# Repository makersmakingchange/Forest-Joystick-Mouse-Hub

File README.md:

# Forest Joystick Mouse Hub

## Overview
The Forest Hub enables a user to connect an analog joystick and up to four assistive switches to emulate a USB Mouse or USB Gamepad. As a USB Mouse, the joystick controls cursor movement and the assistive switches activate the left mouse button, right mouse button, middle mouse button, and scroll. As a USB Mouse, the joystick maps to the joystick/thumbstick and the assistive switches map to the joystick buttons. An additional assistive switch can be attached to the Hub to cycle between three setting slots and change the output mode between USB Mouse mode and USB Gamepad mode.

The device is comprised of a custom printed circuit board, off-the-shelf electronics, and 3D printed parts. The overall cost of materials for a single build is about $100. The individual unit cost cost is closer to $55. 

The Forest Hub is open assistive technology (OpenAT). Under the terms of the open source licenses, the device may be built, used, and improved upon by anyone.

Last updated: 2024-Apr-17
The latest version (V2.1) includes a new easier to use LED jig, updated firmware with center calibration, and updated documentation.
An updated version of the PCB and enclosure has been released (V2.0.1, 2024-Feb-20). The last version of the Forest Hub (v2.0.1) has been built and tested.

MMC Assistive Device Library Listing: https://makersmakingchange.com/s/product/forest-joystick-mouse-hub/01tJR000000E4bdYAC

## OpenAT Joysticks
This design is part of the [OpenAT Joystick Project](https://github.com/makersmakingchange/OpenAT-Joysticks), a collection of open source designs for digital access and adapted gaming.  

## How to Obtain the Device
### 1. Do-it-Yourself (DIY) or Do-it-Together (DIT)

This is an open-source assistive technology, so anyone is free to build it. All of the files and instructions required to build the device are contained within this repository. Refer to the Maker Guide below.

### 2. Request a build of this device

If you would like to obtain a Forest Hub, you may submit a build request through the [MMC Assistive Device Library Listing](https://makersmakingchange.com/s/product/forest-joystick-mouse-hub/01tJR000000E4bdYAC) to have a volunteer maker build the device. As the requestor, you are responsible for reimbursing the maker for the cost of materials and any shipping.

### 3. Build this device for someone else

If you have the skills and equipment to build this device, and would like to donate your time to create the switch for someone who needs it, visit the [MMC Maker Wanted](https://makersmakingchange.com/maker-wanted/) section.

## Build Instructions

### 1. Read through the Maker Guide

The [Maker Guide](/Documentation/Forest_Hub_Maker_Guide.pdf) contains all the necessary information to build the device.

### 2. Use the Maker Checklist
Use the Maker Checklist in the [Maker Guide](/Documentation/Forest_Hub_Maker_Guide.pdf) to confirm details and customization options with the user.

### 3. Order the Custom Printed Circuit Board (PCB)
The manufacturing files for the PCB are located in the [PCB_Build_Files](/Build_Files/PCB_Build_Files/) folder.

### 4. Order the Off-The-Shelf Components

The [Bill of Materials](/Documentation/Forest_Hub_BOM.xlsx) lists all of the parts and 3D printed components required to build the device. 

### 5. Print the 3D Printable components

The print files can be found in the [/Build_Files/3D_Printing_Files](/Build_Files/3D_Printing/) folder.

### 6.  Assemble the Device

Reference the Assembly Guide section in the [Maker Guide](/Documentation/Forest_Hub_Maker_Guide.pdf) for the tools and steps required to build the device.

## Files
### Documentation
| Document             | Version | Link |
|----------------------|---------|------|
| Design Rationale     | 2.1     | [Forest_Hub_Design_Rationale](/Documentation/Forest_Hub_Design_Rationale.pdf)     |
| Maker Guide          | 2.1     | [Forest_Hub_Maker_Guide](/Documentation/Forest_Hub_Maker_Guide.pdf)     |
| Bill of Materials    | 2.1     | [Forest_Hub_Bill_of_Materials](/Documentation/Forest_Hub_BOM.csv)     |
| User Guide           | 2.1     | [Forest_Hub_User_Guide](/Documentation/Forest_Hub_User_Guide.pdf)    |
| Changelog            | 2.1     | [Changes](Changes.txt)     |

### Design Files
 - [CAD design Files](/Design_Files/CAD_Design_Files)
 - [PCB Design Files](/Design_Files/PCB_Design_Files)

### Build Files
 - [3D Printing Files](/Build_Files/3D_Printing_Files)
 - [PCB Build Files](/Build_Files/PCB_Build_Files/)
 - [Firmware Files](/Build_Files/Firmware_Files)

## License
Copyright (c) 2023 Neil Squire Society.

This repository describes Open Hardware:
 - Everything needed or used to design, make, test, or prepare the Forest Hub is licensed under the [CERN 2.0 Weakly Reciprocal license (CERN-OHL-W v2) or later](https://cern.ch/cern-ohl ) .
 - All software is under the [GNU General Public License v3.0 (GPL-3.0)](https://www.gnu.org/licenses/gpl.html).
 - Accompanying material such as instruction manuals, videos, and other copyrightable works that are useful but not necessary to design, make, test, or prepare the Forest Hub are published under a [Creative Commons Attribution-ShareAlike 4.0 license (CC BY-SA 4.0)](https://creativecommons.org/licenses/by-sa/4.0/) .

You may redistribute and modify this documentation and make products using it under the terms of the [CERN-OHL-W v2](https://cern.ch/cern-ohl).
This documentation is distributed WITHOUT ANY EXPRESS OR IMPLIED WARRANTY, INCLUDING OF MERCHANTABILITY, SATISFACTORY QUALITY AND FITNESS FOR A PARTICULAR PURPOSE.
Please see the CERN-OHL-W v2 for applicable conditions.

Source Location: https://github.com/makersmakingchange/Forest-Joystick-Mouse-Hub

## Attribution

The [Adafruit QT Py](http://www.adafruit.com/products/4600) development board was designed by Limor Fried/Ladyada from Adafruit. The PCB design is [available open source](https://github.com/adafruit/Adafruit-QT-Py-PCB) under a CC-BY-SA license.

The concept for the Forest Hub was based on the [Enabled Controller Mini](https://github.com/milador/Enabled-Controller-Mini) by [Milador](https://github.com/milador).

### Contributors
- Jake McIvor, Neil Squire Society. Concept generation, enclosure design, schematic and PCB design, coding, documentation, testing.
- Milad Ha, Neil Squire Society. Schematic and PCB design, coding.
- Josie Versloot, Neil Squire Society. Concept generation, coding, documentation.
- Derrick Andrews, Neil Squire Society. Schematic design.
- Stephen Moyer, Neil Squire Society. Concept generation.
- Tyler Fentie, Neil Squire Society. Concept generation

## Open Source Hardware Certification

The Forest Hub has been certified as open source hardware by the Open Source Hardware Association under the OSHWA UID [CA000033](https://certification.oshwa.org/ca000033.html).

---
<!-- ABOUT MMC START -->
## About Makers Making Change

Makers Making Change is a program of [Neil Squire](https://www.neilsquire.ca/), a Canadian non-profit that uses technology, knowledge, and passion to empower people with disabilities.

Makers Making Change leverages the capacity of community based Makers, Disability Professionals and Volunteers to develop and deliver affordable Open Source Assistive Technologies.

 - Website: [www.MakersMakingChange.com](https://www.makersmakingchange.com/)
 - GitHub: [makersmakingchange](https://github.com/makersmakingchange)
 - Bluesky: [@makersmakingchange.bsky.social](https://bsky.app/profile/makersmakingchange.bsky.social)
 - Instagram: [@makersmakingchange](https://www.instagram.com/makersmakingchange)
 - Facebook: [makersmakechange](https://www.facebook.com/makersmakechange)
 - LinkedIn: [Neil Squire Society](https://www.linkedin.com/company/neil-squire-society/)
 - Thingiverse: [makersmakingchange](https://www.thingiverse.com/makersmakingchange/about)
 - Printables: [MakersMakingChange](https://www.printables.com/@MakersMakingChange)

### Contact Us
For technical questions, to get involved, or to share your experience we encourage you to [visit our website](https://www.makersmakingchange.com/) or [contact us](https://www.makersmakingchange.com/s/contact).
<!-- ABOUT MMC END -->

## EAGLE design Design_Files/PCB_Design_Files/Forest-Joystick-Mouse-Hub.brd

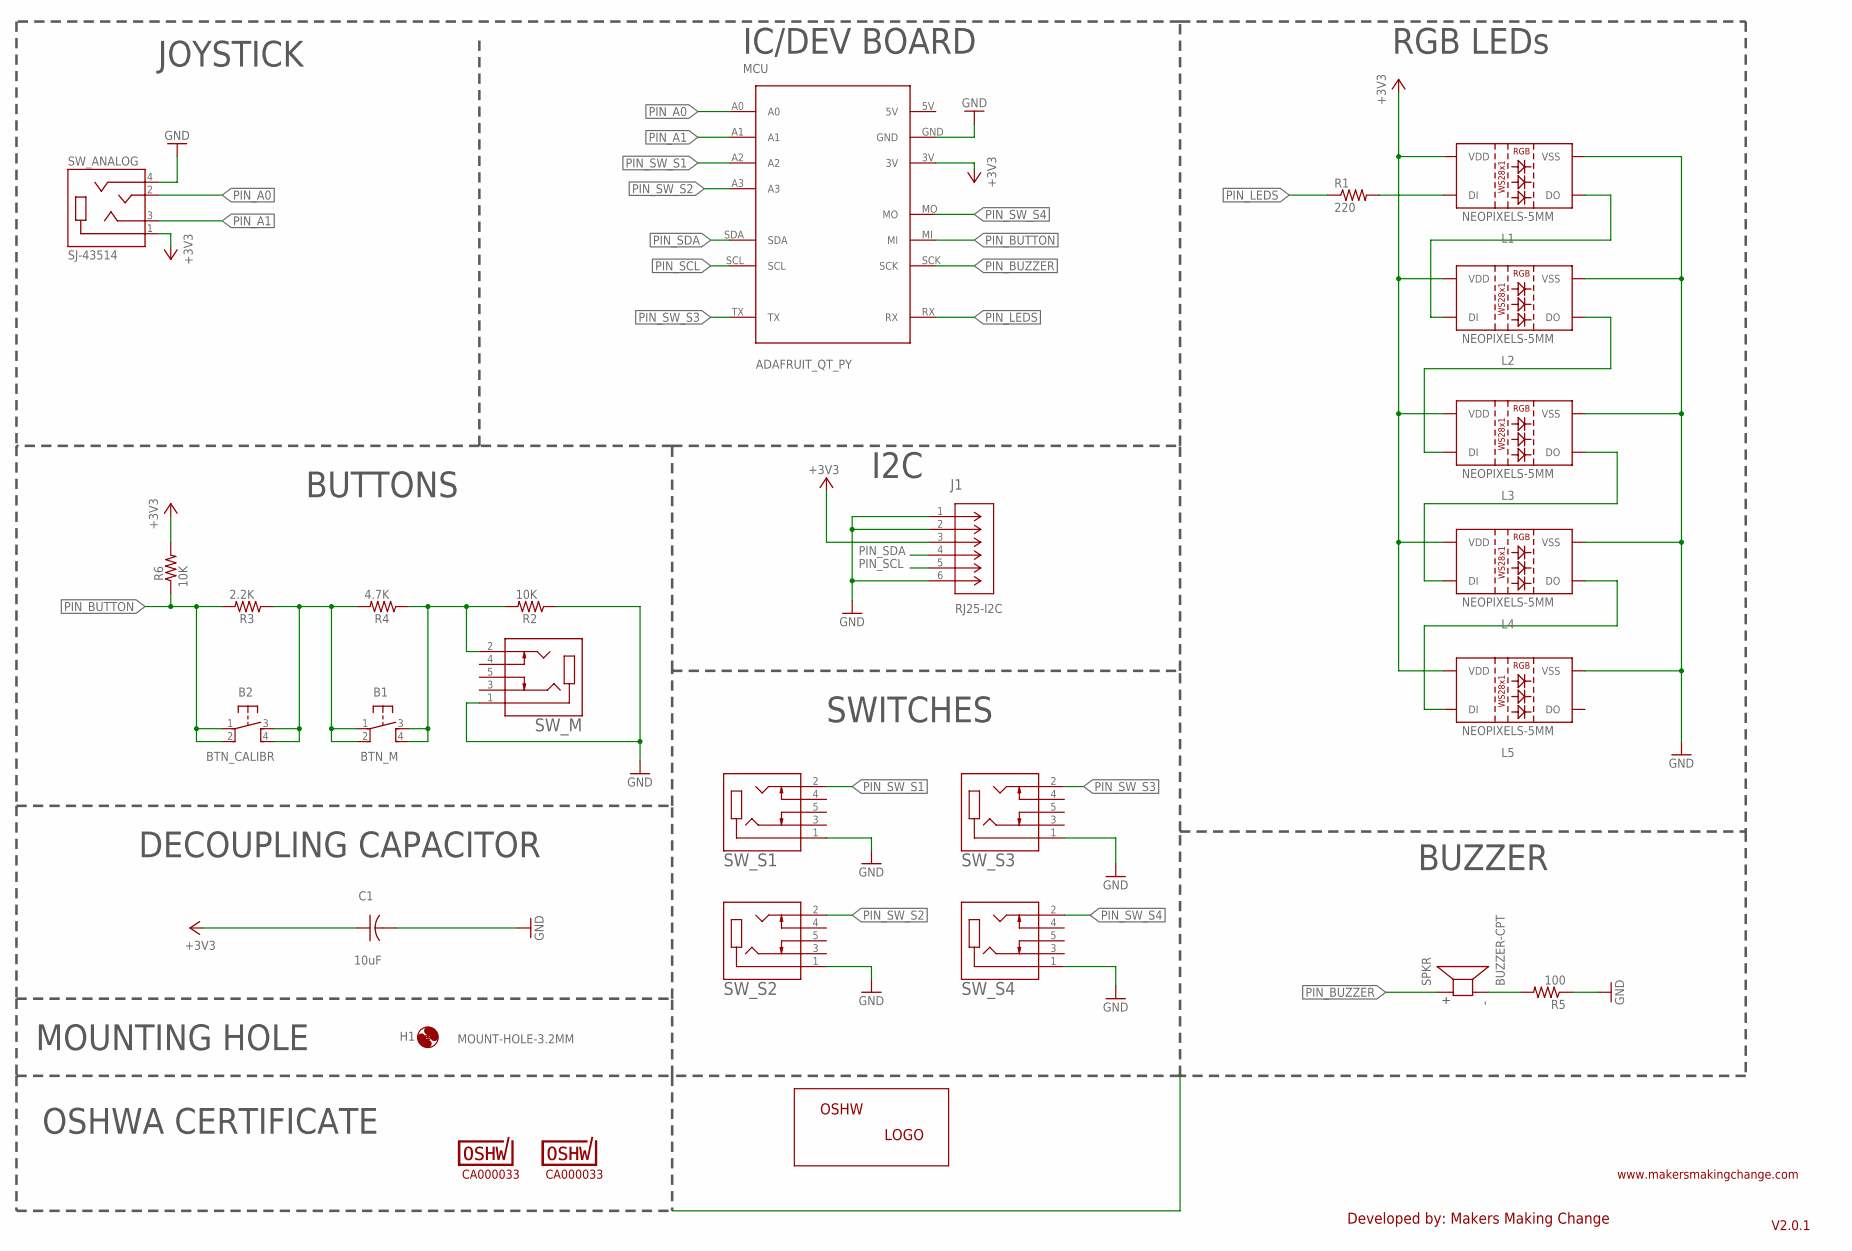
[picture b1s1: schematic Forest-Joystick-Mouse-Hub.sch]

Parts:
B1: BTN_M; B3F-5050
B2: BTN_CALIBR; B3F-5050
C1: 10uF; CAP-050-030X075
H1: MOUNT-HOLE-3.2MM; HOLE-3.2MM
J1: 5555165-1; CONN6_5555165-1
L1, L2, L3, L4, L5: NEOPIXELS-5MM
LOGO-OSHWA: CA000033; OSHWA-CERT-SMALL-SILK
MCU: ADAFRUIT_QT_PY; QT_PY
R1: 220; RESISTOR_0206/8
R2, R6: 10K; RESISTOR_0206/8
R3: 2.2K; RESISTOR_0206/8
R4: 4.7K; RESISTOR_0206/8
R5: 100; RESISTOR_0206/8
SPKR: BUZZER-CPT; CUI_CPT-1255C-090
SW_ANALOG: SJ-43514; CUI_SJ-43514
SW_M: CUI_SJ1-3535NGSJ1-3535NG; CUI_SJ1-3535NG
SW_S1, SW_S2, SW_S3, SW_S4: CUI_SJ1-3535NGSJ1-3535NG; CUI_SJ1-3535NG
U$3: OSHW_LOGO-XSM; OSHW_X-SMALL_LOGO
U$4: CA000033; OSHWA-CERT-SMALL-SILK

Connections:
+3V3: C1.1, J1.3, L1.P2 (VDD), L2.P2 (VDD), L3.P2 (VDD), L4.P2 (VDD), L5.P2 (VDD), MCU.3V, R6.2, SW_ANALOG.1 (SLEEVE)
GND: C1.2, J1.1, J1.2, J1.6, L1.P3 (VSS), L2.P3 (VSS), L3.P3 (VSS), L4.P3 (VSS), L5.P3 (VSS), MCU.GND, R2.1, R5.1, SW_ANALOG.4 (RING2), SW_M.1, SW_S1.1, SW_S2.1, SW_S3.1, SW_S4.1
unnamed: B1.1, B1.2, B2.3, B2.4, R3.1, R4.2
unnamed: L1.P4 (DO), L2.P1 (DI)
unnamed: B1.3, B1.4, R2.2, R4.1, SW_M.2
unnamed: L2.P4 (DO), L3.P1 (DI)
unnamed: L3.P4 (DO), L4.P1 (DI)
unnamed: L4.P4 (DO), L5.P1 (DI)
unnamed: L1.P1 (DI), R1.2
unnamed: R5.2, SPKR.N
PIN_A0: MCU.A0, SW_ANALOG.2 (TIP)
PIN_A1: MCU.A1, SW_ANALOG.3 (RING1)
PIN_BUTTON: B2.1, B2.2, MCU.MI, R3.2, R6.1
PIN_BUZZER: MCU.SCK, SPKR.P
PIN_LEDS: MCU.RX, R1.1
PIN_SCL: J1.5, MCU.SCL
PIN_SDA: J1.4, MCU.SDA
PIN_SW_S1: MCU.A2, SW_S1.2
PIN_SW_S2: MCU.A3, SW_S2.2
PIN_SW_S3: MCU.TX, SW_S3.2
PIN_SW_S4: MCU.MO, SW_S4.2

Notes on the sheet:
V2.0.1
Developed by: Makers Making Change
www.makersmakingchange.com
BUZZER
RGB LEDs
BUTTONS
I2C
IC/DEV BOARD
SWITCHES
JOYSTICK
MOUNTING HOLE
DECOUPLING CAPACITOR
OSHWA CERTIFICATE

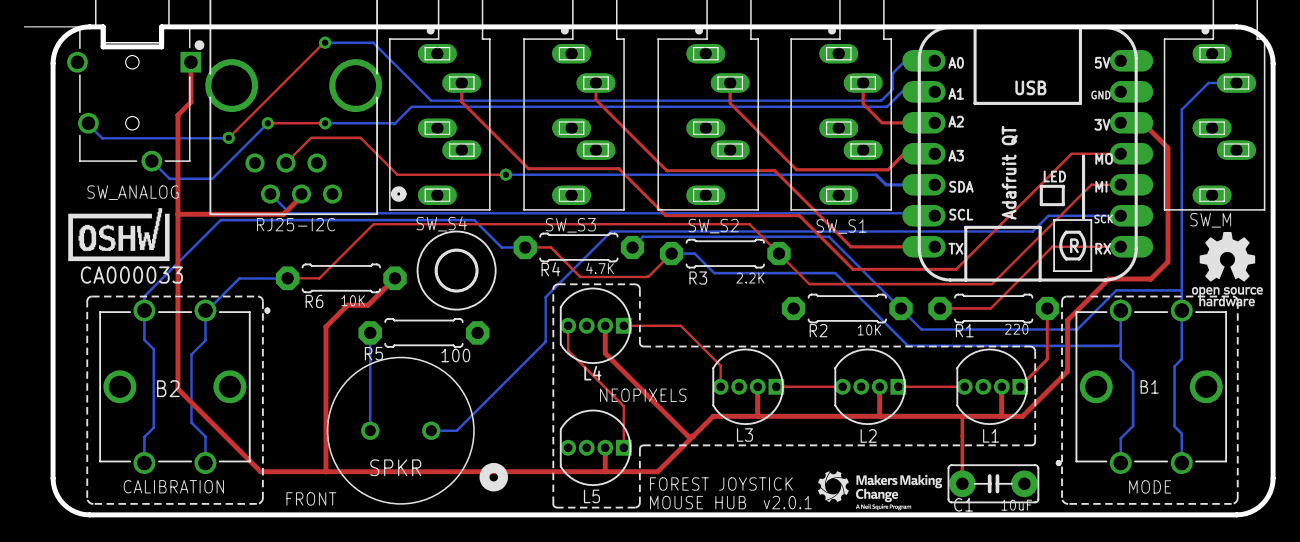
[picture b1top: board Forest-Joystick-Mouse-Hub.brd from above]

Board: 2 copper layers, 102.3 x 40.0 mm, 28 parts (1 on the bottom side), 21 nets.

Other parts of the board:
U$5: MMC_X-SMALL_LOGO

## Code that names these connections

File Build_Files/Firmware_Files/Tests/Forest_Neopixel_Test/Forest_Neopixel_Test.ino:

#include <Adafruit_NeoPixel.h> //Lights on QtPy

// ==================== Pin Assignment =================

#define PIN_JOYSTICK_X    A0
#define PIN_JOYSTICK_Y    A1
#define PIN_SW_S1         A2
#define PIN_SW_S2         A3
#define PIN_SW_S3         A6 //TX
#define PIN_SW_S4         A10 //MO
#define PIN_BUTTON        A9 //MI
#define PIN_LEDS          A7 //RX
#define PIN_BUZZER        A8 //SCK

Adafruit_NeoPixel leds(5, PIN_LEDS,NEO_GRB + NEO_KHZ800);  // Create a pixel strand with 5 pixels on QtPy
int ledsBrightness = 50;

void setup() {
  leds.begin();
  leds.setBrightness(ledsBrightness);
  leds.setPixelColor(0,leds.Color(0,255,0)); //red g r b
  leds.setPixelColor(1,leds.Color(165,255,0)); //orange
  leds.setPixelColor(2,leds.Color(255,255,0)); //yellow
  leds.setPixelColor(3,leds.Color(255,0,0)); //green
  leds.setPixelColor(4,leds.Color(0,0,255)); //blue
  leds.show();

}

void loop() {
  // put your main code here, to run repeatedly:

}

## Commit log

2023-09-29 v1.0 Update
2023-09-30 Update basic user guide.
2023-09-30 PCB Files cleanup
2023-10-01 Update resistor size
2023-10-01 Adjustable cursor speed
    Basic implementation of adjustable cursor speed via code or API
2023-10-01 Update Forest_Hub_Firmware.ino
    Add device number to API
2023-10-01 Update Forest_Hub_Firmware.ino
    Clean up old cursor speed variable.
2023-10-01 Update Forest_Button_Test.ino
    Working multi-button via analog pin
2023-10-01 Clean-up switch labels.
2023-10-01 Setup default values for memory
2023-10-01 Add LED Brightness parameter
2023-10-01 Add multi-button handling via PIN_BUTTONS
2023-10-01 Update Forest_Button_Test.ino
    Clean-up
2023-10-01 Create Forest_Reset_Test.ino
    Basic long-press software reset.
2023-10-13 Update BOM
    Use two 7p headers rather than cheaper one you need to cut.
2023-10-13 Add Open Source Hardware certification
2023-10-25 Update Forest_Hub_Firmware.ino
    Added variable for slot index in Flash memory
2023-10-25 Revert "Update Forest_Hub_Firmware.ino"
2023-10-25 Added slot structure
2023-10-28 PCB Updates
    - Footprint for larger resistors
    - Added OSHWA Certification logo
    - Updated Gerbers
2023-10-28 Clean-up PCB build files
2023-10-31 Added saving slot to memory and loading slot on startup
2023-10-31 Changed logic for buttons and added slot functionality
2023-11-03 Fixed joystick directions and added some mode change functionality
2023-11-03 Changed LED colour and default slot
2023-11-03 Create Resistor_Network.xlsx
    Add spreadsheet for calculating nominal tolerances for analog resistor network.
2023-11-03 Update Forest_Hub_Design_Rationale.docx
    Add details on resistor network
2023-11-03 Update Forest_Hub_Firmware.ino
    Update resistor network values.
2023-11-07 Update Forest_Hub_Firmware.ino
    Add basic software reset
2023-11-07 Update Forest_Hub_Firmware.ino
    comments.
2023-11-07 Added mode change functionality using soft reset
2023-11-25 PCB and Enclosure Update
    - Swapped RJ11 connector to match Sparkfun Breakout board / reduce number of parts
    - Swapped RJ11 wiring to match QWIIC adapter board / LipSync
    - Modified USB Knockout on Case
    -
2023-11-27 Update Forest_Hub_Firmware.ino
    rename slotChange to incrementSlot
2023-11-27 Update Forest_Hub_Firmware.ino
    Remove secondary load cursorspeed
2023-11-27 Basic slot implementation
    - added slot zero
    - added API for slot number change
2023-11-27 Update Forest_Hub_Firmware.ino
    default slot to 0
2023-11-27 Update Forest_Hub_Firmware.ino
    rename mouse slots
    fix cursor speed update with slot update
2023-11-27 Update Forest_Hub_Firmware.ino
    write slot to memory so it is persistent
2023-12-07 Savepoint 2023-Dec-7
2023-12-11 Updated with correct joystick directions
2024-01-08 Fixed some missing references
2024-01-10 Minor PCB updates
2024-01-15 Update OKH-ForestJoystickMouseHub.yml
    Fix Milad's surname
    minor edits.
2024-01-24 V2.0 Update
2024-02-16 Update Forest_Hub_Firmware.zip
    Update convenience zip folder to match latest firmware
2024-02-16 Update version and date in code
2024-02-20 Update Forest_Hub_Firmware.ino
    Fix calibration variables.
2024-02-20 Updated test code thresholds
2024-02-20 Updated documentation
2024-02-23 Added debug and api functions
2024-03-13 Basic neutral calibration working on startup
2024-03-14 Basic neutral calibration working through API and button press
2024-03-18 Functional neutral calibration that allows for output of full extents
2024-03-18 Updated zip file
2024-03-18 Added mode dependent buzzer noise on startup
2024-03-18 Updated firmware zip file
2024-03-18 Remove old PCB design files
2024-03-18 Update Forest_Hub_Firmware.ino
    Add GetJoystickFunction to API
2024-03-18 Update Forest_Hub_Firmware.ino
    comment clean up
2024-03-18 Update Forest_Hub_Firmware.ino
    Add Arduino.h library for future PlatformIO expansion
2024-03-18 Update Forest_Hub_Firmware.ino
    Up rev
2024-03-19 Update Forest_Hub_Firmware.ino
    Add constants for tones
2024-03-20 Update Forest_Hub_Firmware.ino
    Fixed bug for low cursor speeds, improved mouse movement resolution
2024-04-12 Add updated PCB images
    PCB V2.0.1
2024-04-12 Add additional PCB screenshots
2024-04-14 Two additional photos
2024-04-14 Maker Guide Update
2024-04-16 Updated Maker Guide formatting
2024-04-17 Updated User Guide and related resources
2024-04-17 Update User Guide
    Update copyright years
    Add Joystick links
    Minor editing
2024-04-18 Replace default LED Spacer
2024-04-18 Update design rationale
2024-04-18 Remove outdated PCB schematic and board pdfs
2024-04-18 V2.1
2024-04-23 Fixed bug
    Wasn't showing slot LED after neutral calibration
2024-04-29 Updated Gerber files
    Update Gerber files to v2.0.1.
    Remove old Gerber files.
2024-04-29 Add PCB instructions to Maker Guide
2025-04-10 Add Update About MMC GitHub Action
2025-04-12 Update About MMC Section
2025-06-16 Update Maker Guide testing section
    Added note to change to Gamepad mode before testing using USB Gamepad Tester on PC or using XAC.
2025-08-07 Rename OKH-ForestJoystickMouseHub.yml to okh-ForestJoystickMouseHub.yml
2026-01-05 Update file paths to use 'main' branch

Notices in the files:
README.md:
List of open source licenses. Hardware: CERN-OHL-W-2.0, Software: GPL-3.0-or-later, Documentation: CC-BY-SA-4.0.
parts and their libraries:
COPYRIGHT: Copyright (C) 2023 Ultra Librarian. All rights reserved.
SparkFun-Aesthetics: Licensing: Creative Commons ShareAlike 4.0 International - https://creativecommons.org/licenses/by-sa/4.0
